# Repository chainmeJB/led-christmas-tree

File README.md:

# LED Christmas Tree

A Christmas tree-shaped LED board powered by USB-C and a rechargeable Li-ion 18650 battery, where two groups of colored LEDs blink alternately using a transistor astable multivibrator.

**Author:** Benediuk Yullia. **Revision:** 1.0. **Tools:** KiCad 10 and Fusion.

## How it works

Power comes from a USB-C charger at 5 V. A charger chip (MCP73831) takes this voltage and charges a Li-ion 18650 cell. The cell is connected to the output of the charger, and through an ON/OFF switch it supplies the blinking circuit. This means the tree runs from the battery, and when the cable is plugged in, the battery is charged at the same time and the tree keeps blinking.

The blinking is made by an astable multivibrator, an analog circuit without a microcontroller and without any code. It has two transistors, and each transistor switches one group of three LEDs. The collector of each transistor is connected through a capacitor to the base of the other one. Because of this, when one transistor turns on, it turns the other one off, then the capacitors slowly recharge through the base resistors, and after a fraction of a second the transistors swap roles. So the left group and the right group of LEDs light up one after another, about 2 to 3 times per second.

## Schematic

The schematic is divided into blocks:

- **USB-C input.** The connector J1 gives 5 V. Two 5.1 kΩ resistors from the CC1 and CC2 pins to ground tell the charger that a device is connected, so it provides 5 V.
- **Charger.** The MCP73831 chip charges the cell with about 500 mA, the current is set by the 2 kΩ resistor on its PROG pin. Two 10 µF capacitors smooth the input and the output.
- **Charge indicator.** A green LED with a 1 kΩ resistor lights up while the battery is charging.
- **Battery and switch.** One 18650 cell with a built-in protection board and a slide switch that turns the tree on and off. The battery can be charged with the switch off.
- **Multivibrator.** Two MMBT3904 transistors, two 47 µF capacitors connected crosswise, and two 10 kΩ base resistors.
- **LED groups.** Six LEDs, three on each transistor: red, orange and yellow. Every LED has its own 330 Ω resistor, which limits its current to about 4.5 mA.

## PCB

| Front | Back |
|---|---|
|  |  |

| Front (3D) | Back (3D) |
|---|---|
|  |  |

The board is cut in the shape of a three-tier tree, 100 × 140 mm, two copper layers, with a hanging hole at the top.

- **LEDs.** The left group sits on the left half of the tree and the right group on the right half. On each tier there is one pair of LEDs with the same color (red on the top tier, orange in the middle, yellow on the bottom), so the tree blinks from left to right.
- **Power line.** The positive supply goes along the center of the tree and feeds the resistor of every LED. The lines of the LED groups run along the outer sides of the tree.
- **Charger and switch.** They are placed at the bottom of the tree, near the trunk. The charge indicator LED is marked CHG on the silkscreen.
- **USB-C.** The connector is on the right edge of the trunk, so the cable comes in from the side of the stand.
- **Back side.** The whole back layer is a ground plane. The 18650 battery holder is mounted on the back along the trunk, with the negative contact at the top and the positive contact at the bottom.
- **Silkscreen.** The title, the author, the revision, the date, the marks ON/OFF, CHG and USB-C 5V, and a warning "PROTECTED 18650 ONLY" on the back.

## Stand

| Front | Back | Side | Isometric
|---|---|---|---|
|  |  |  | 

The board stands upright in a simple 3D-printed block of 90 × 70 × 14 mm. The trunk of the tree goes into a slot 1.9 mm wide, and a trough on the right side leaves room for the USB-C jack and the cable plug. The battery holder stays behind the board, above the block, and the block is extended to the back so that the tree does not tip over. The title and the revision are engraved on the front.

## Files

- `kicad/` contains the schematic and the PCB. Open `ChristmasTree.kicad_pro` in KiCad 10.
- `enclosure/` contains the Fusion project, the whole assembly as a STEP file, and the stand for printing as an STL file.
- `docs/schematic.pdf` is the schematic in full size.
- `images/` contains the screenshots used in this file.

## Status and notes

This is a design-stage course project: the board is not manufactured. The blink rate and the LED currents are calculated, not measured. Only a protected 18650 cell may be used, because the circuit has no battery protection of its own. The LEDs are red, orange and yellow, because blue and white ones need about 3 V and would be dim when the battery is almost empty.

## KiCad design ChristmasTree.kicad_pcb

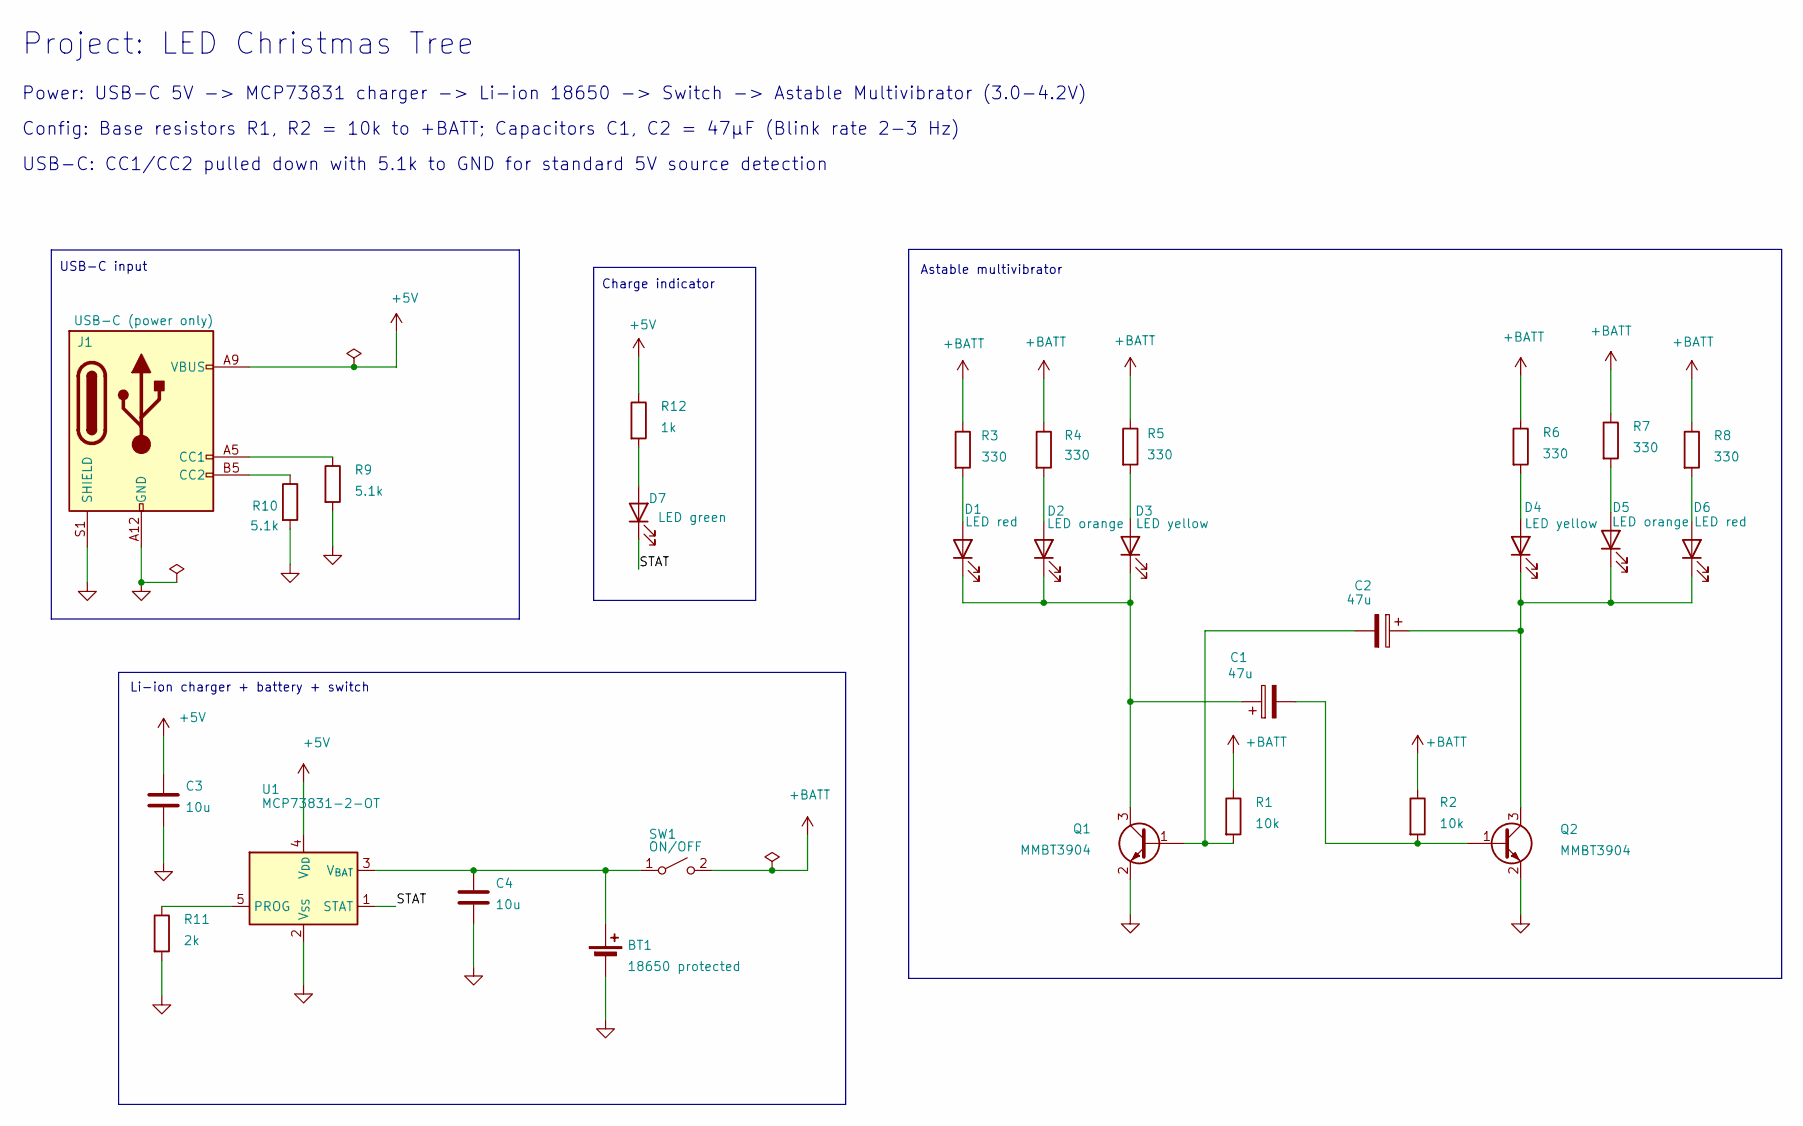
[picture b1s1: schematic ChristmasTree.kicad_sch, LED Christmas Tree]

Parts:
BT1: 18650 protected; BatteryHolder_Keystone_1042_1x18650
C1, C2: 47u; CP_Elec_5x5.4
C3, C4: 10u; C_0805_2012Metric
D1, D6: LED red; LED_0805_2012Metric
D2, D5: LED orange; LED_0805_2012Metric
D3, D4: LED yellow; LED_0805_2012Metric
D7: LED green; LED_0805_2012Metric
J1: USB-C (power only); USB_C_Receptacle_GCT_USB4125-xx-x_6P_TopMnt_Horizontal
Q1, Q2: MMBT3904; SOT-23
R1, R2: 10k; R_0805_2012Metric
R3, R4, R5, R6, R7, R8: 330; R_0805_2012Metric
R9, R10: 5.1k; R_0805_2012Metric
R11: 2k; R_0805_2012Metric
R12: 1k; R_0805_2012Metric
SW1: ON/OFF; SW_SPDT_PCM12
U1: MCP73831-2-OT; SOT-23-5

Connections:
+5V: C3.1, J1.A9 (VBUS), J1.B9 (VBUS), R12.1, U1.4 (V_{DD})
+BATT: R1.1, R2.1, R3.1, R4.1, R5.1, R6.1, R7.1, R8.1, SW1.2 (B)
/STAT: D7.1 (K), U1.1 (STAT)
GND: BT1.2 (-), C3.2, C4.2, J1.A12 (GND), J1.B12 (GND), J1.S1 (SHIELD), Q1.2 (E), Q2.2 (E), R9.2, R10.2, R11.2, U1.2 (V_{SS})
unnamed: BT1.1 (+), C4.1, SW1.1 (A), U1.3 (V_{BAT})
unnamed: D1.2 (A), R3.2
unnamed: C1.1, D1.1 (K), D2.1 (K), D3.1 (K), Q1.3 (C)
unnamed: D2.2 (A), R4.2
unnamed: D3.2 (A), R5.2
unnamed: D4.2 (A), R6.2
unnamed: C2.1, D4.1 (K), D5.1 (K), D6.1 (K), Q2.3 (C)
unnamed: D5.2 (A), R7.2
unnamed: D6.2 (A), R8.2
unnamed: D7.2 (A), R12.2
unnamed: J1.A5 (CC1), R9.1
unnamed: J1.B5 (CC2), R10.1
unnamed: C2.2, Q1.1 (B), R1.2
unnamed: C1.2, Q2.1 (B), R2.2
unnamed: R11.1, U1.5 (PROG)

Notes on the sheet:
Config: Base resistors R1, R2 = 10k to +BATT; Capacitors C1, C2 = 47µF (Blink rate 2-3 Hz)
Power: USB-C 5V -> MCP73831 charger -> Li-ion 18650 -> Switch -> Astable Multivibrator (3.0-4.2V)
Li-ion charger + battery + switch
USB-C input
USB-C: CC1/CC2 pulled down with 5.1k to GND for standard 5V source detection
Astable multivibrator
Charge indicator
Project: LED Christmas Tree

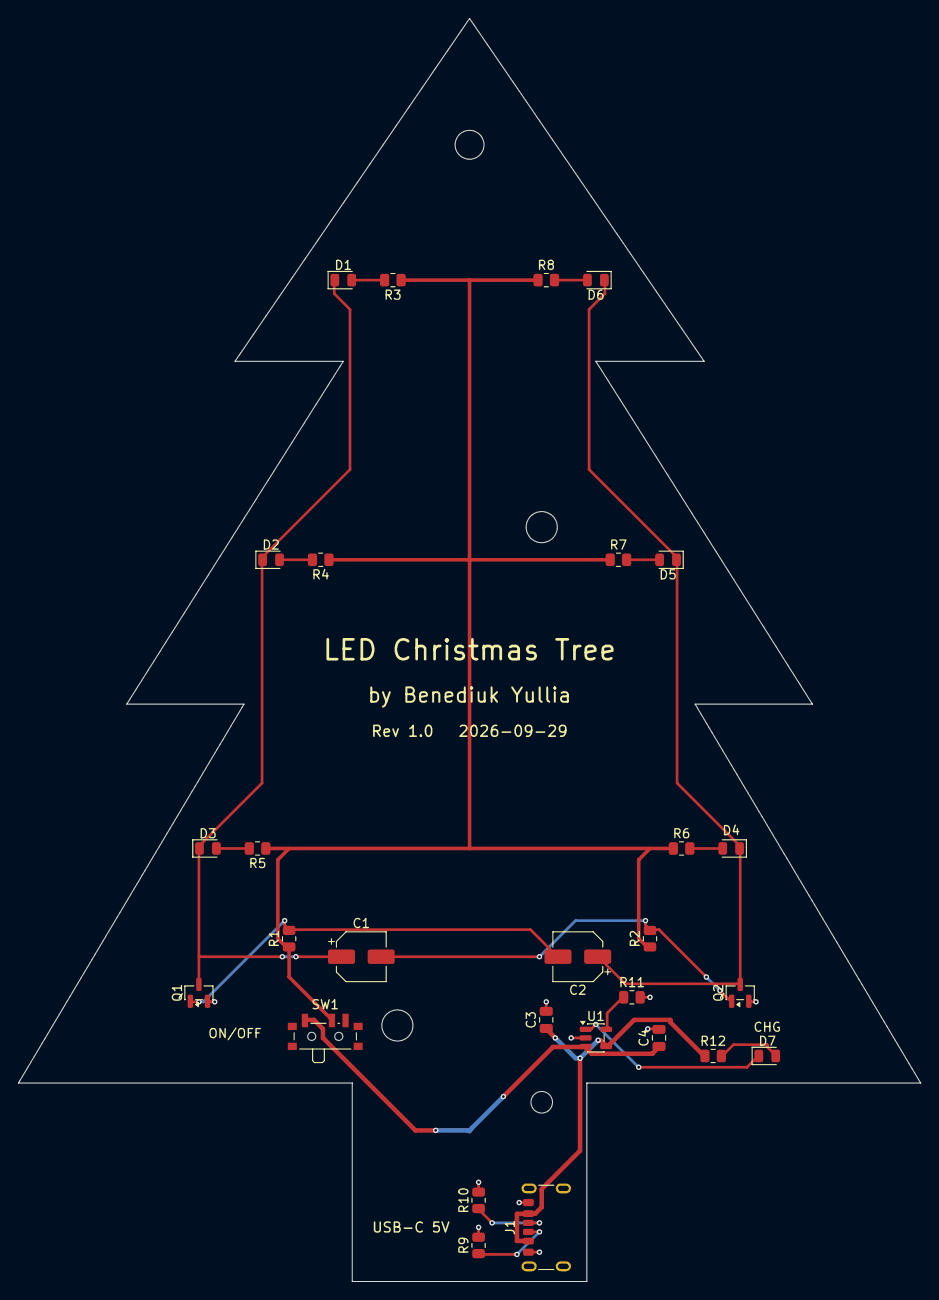
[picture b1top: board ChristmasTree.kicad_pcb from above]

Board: 2 copper layers, 100.0 x 140.0 mm, 30 parts (1 on the bottom side), 19 nets.

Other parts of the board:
H1: Hanging hole; MountingHole_3.2mm_M3
